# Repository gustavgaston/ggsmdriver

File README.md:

# GGSMDriver

A small, reusable stepper driver module: STM32G0B1 + TMC2209, one 9–24 V supply
and a 4-wire motor on one row of screw terminals along one edge, and USB-C for serial
and firmware upload. The board is 4 layers, 55×45 mm, with every
part on top, for JLCPCB assembly.

## Layout

| Path | What |
|---|---|
| `requirements.md` | Circuit spec, pin map, parts with LCSC numbers, confirmed decisions |
| `PLAN.md` | Milestones |
| `HANDOFF.md` | Current state and how to regenerate everything (start here when resuming) |
| `hardware/ggsmdriver.py` | The design as Python: parts, pin→net map, PCB placement |
| `hardware/ggsmdriver.kicad_sym` | Custom TMC2209 symbol |
| `kicad/` | Generated KiCad project (schematic, PCB, PDF) and `reports/` |
| `kicad/fab/` | JLCPCB gerbers zip, BOM and placement (CPL) files |
| `firmware/` | STM32 HAL firmware: ggstepper core + Automato over USB serial (see its README) |

The KiCad files are generated by [autopcb](https://github.com/gustavgaston/autopcb)
from `hardware/ggsmdriver.py`; hand edits in KiCad are lost on regeneration.
They are KiCad 7 format and open in KiCad 10.

## Status

- Schematic: done (ERC clean in KiCad 10).
- PCB: generated and fully routed as a practice run; routing, placement and
  silkscreen to be reworked later.
- Fab files: generated.
- Firmware: ported and building; untested on hardware.

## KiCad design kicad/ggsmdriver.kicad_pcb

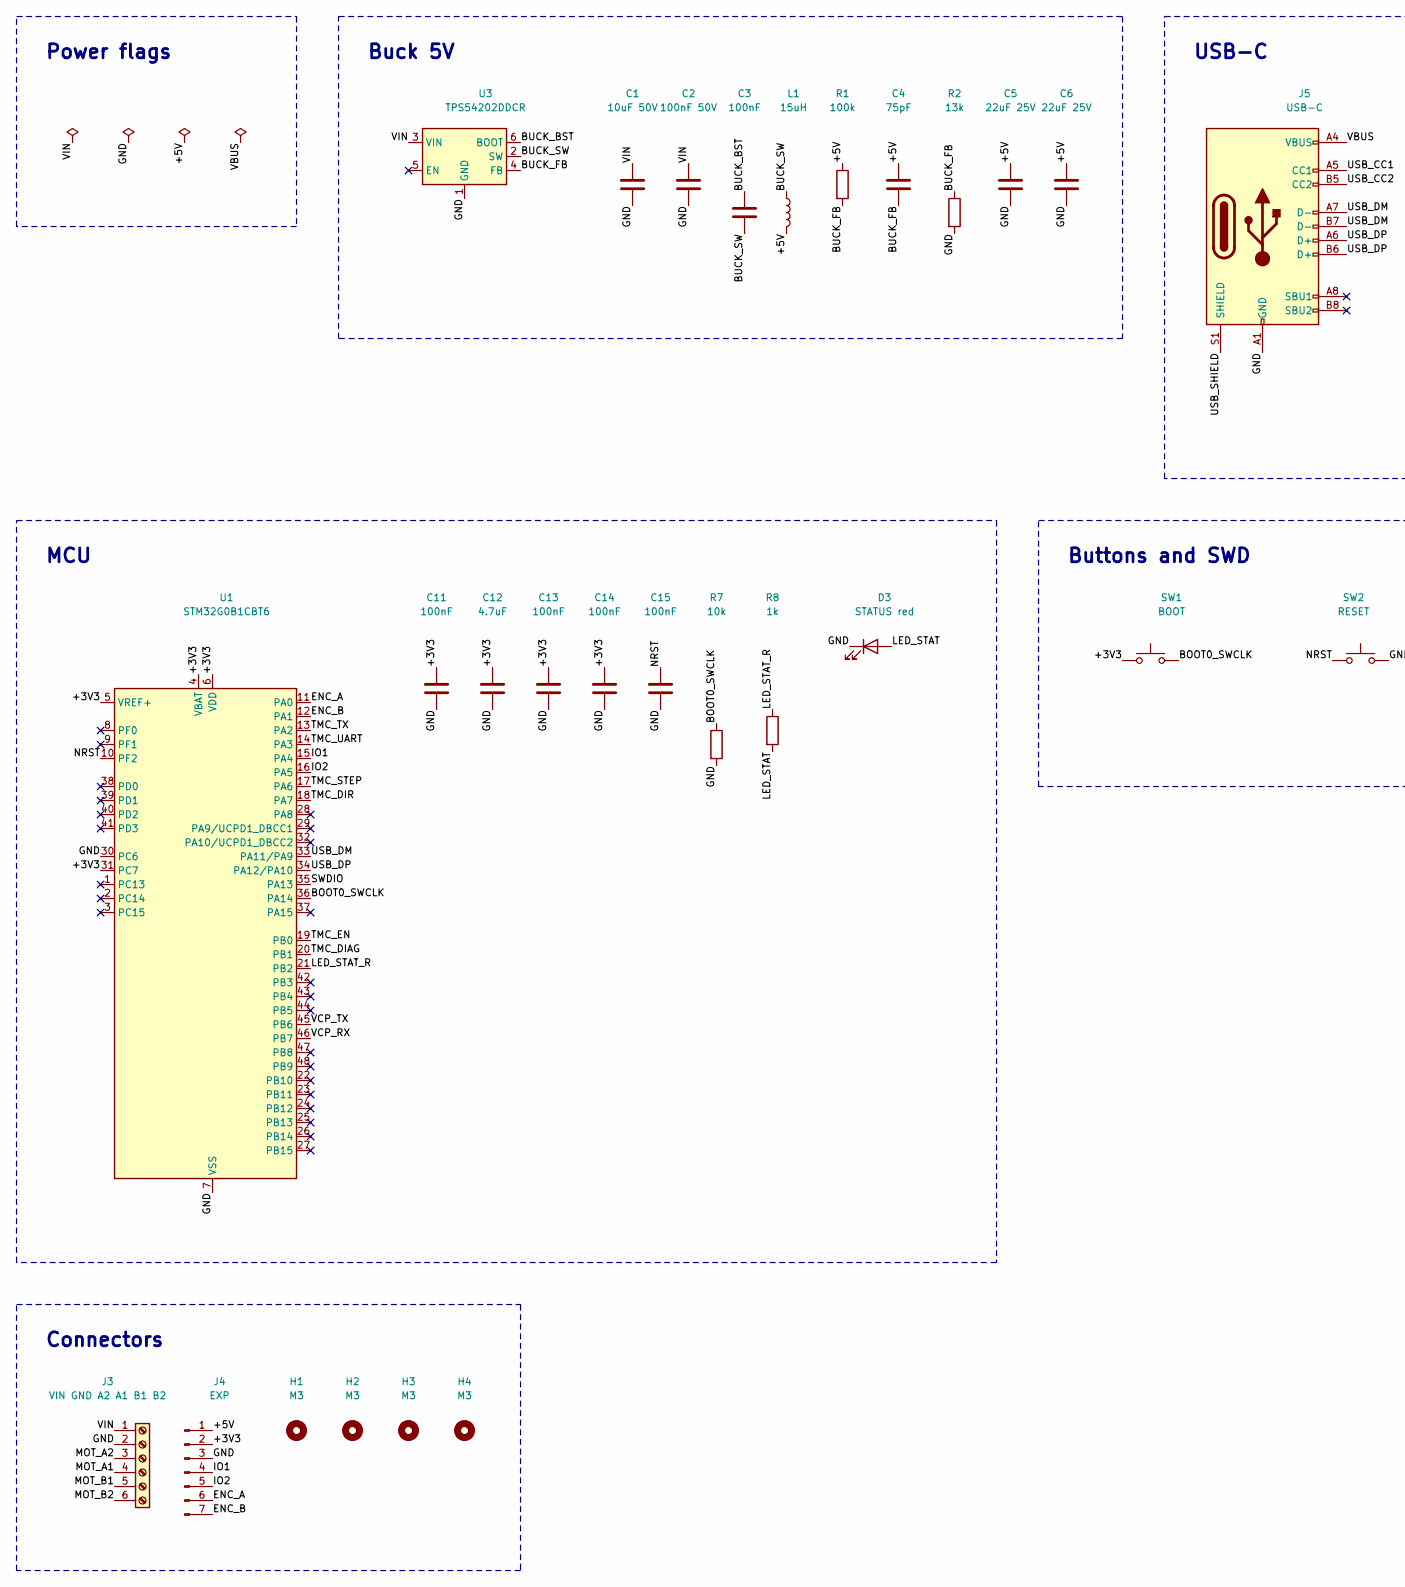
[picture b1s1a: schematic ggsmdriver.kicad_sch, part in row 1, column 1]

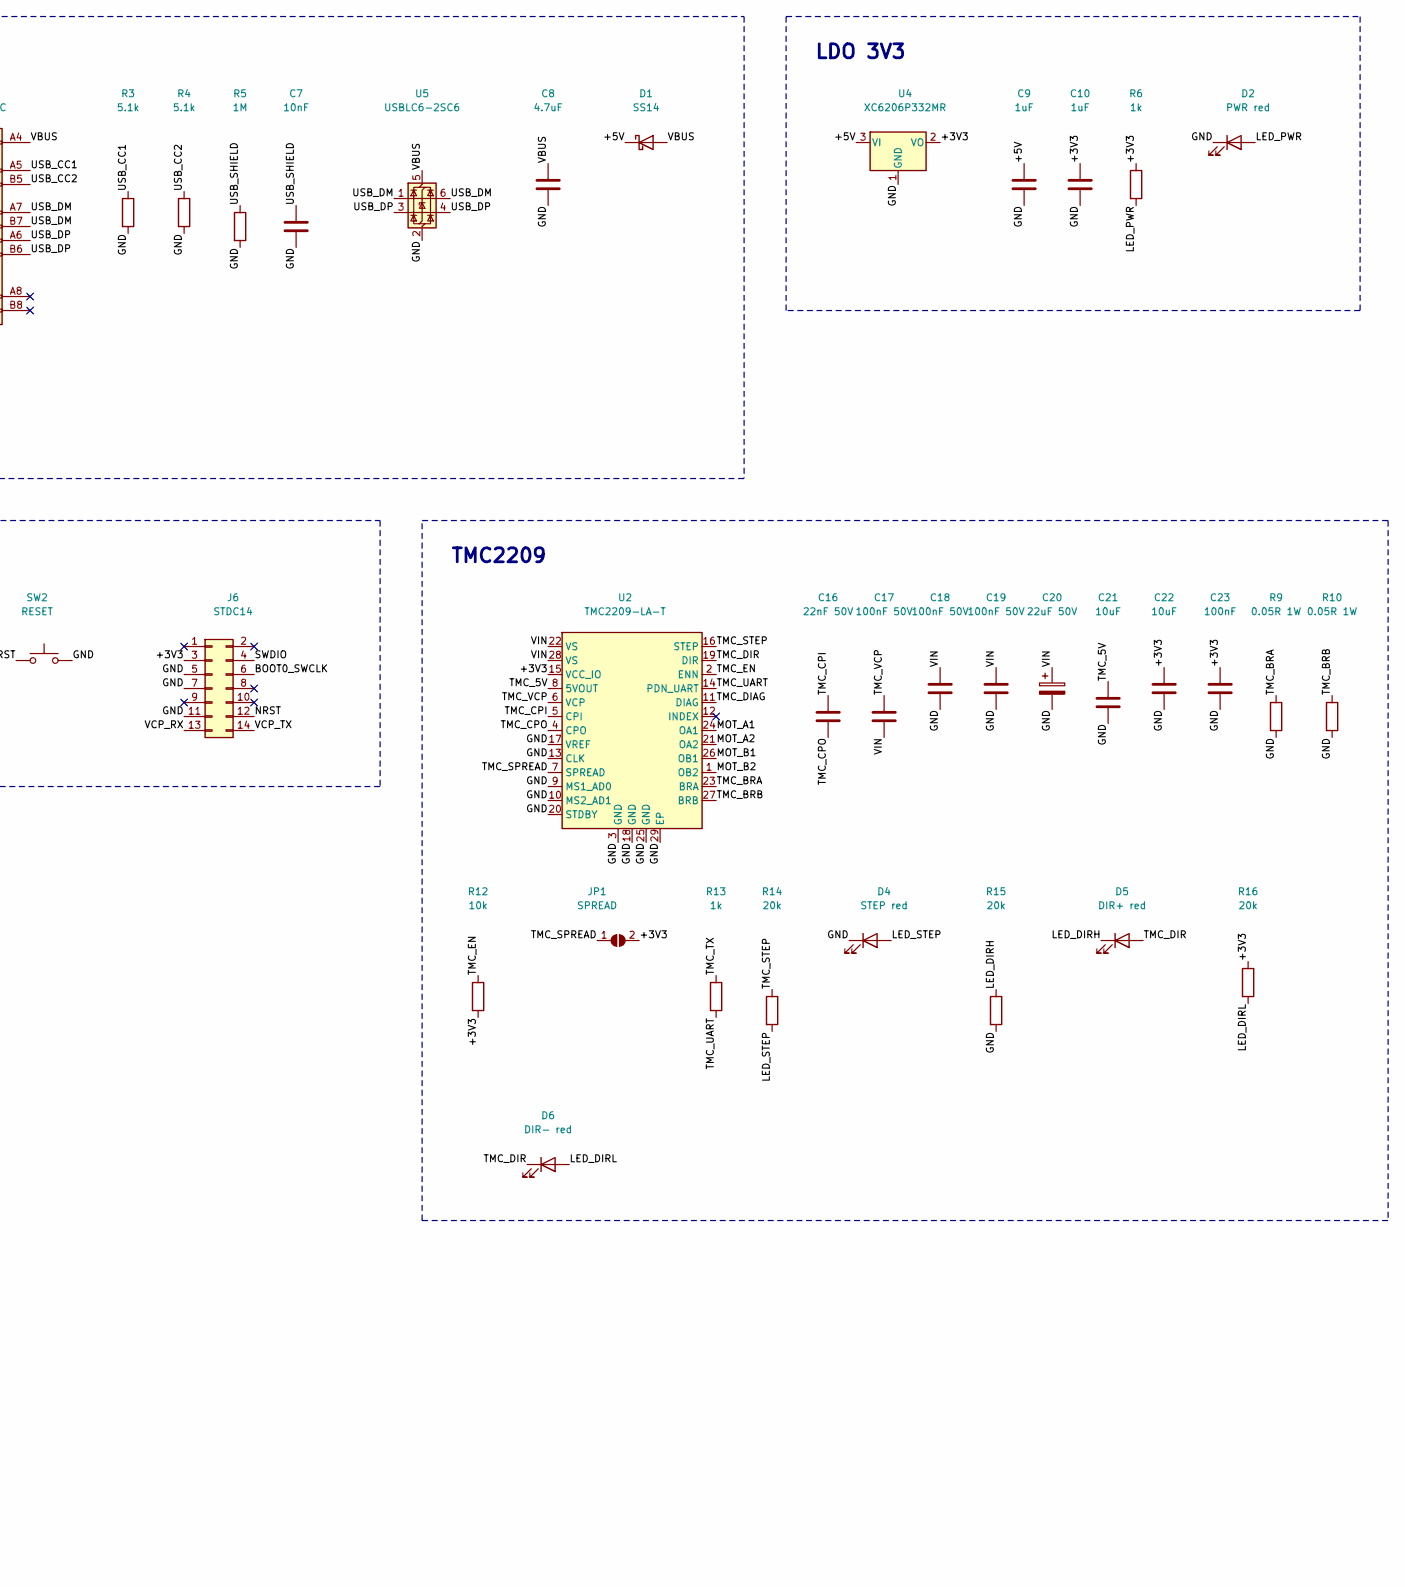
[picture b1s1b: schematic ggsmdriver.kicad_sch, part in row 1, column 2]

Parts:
C1: 10uF 50V; C_1206_3216Metric; LCSC C13585
C2, C17, C18, C19: 100nF 50V; C_0603_1608Metric; LCSC C14663
C3, C11, C13, C14, C15, C23: 100nF; C_0603_1608Metric; LCSC C14663
C4: 75pF; C_0603_1608Metric; LCSC C1681
C5, C6: 22uF 25V; C_1206_3216Metric; LCSC C12891
C7: 10nF; C_0603_1608Metric; LCSC C57112
C8, C12: 4.7uF; C_0805_2012Metric; LCSC C1779
C9, C10: 1uF; C_0603_1608Metric; LCSC C15849
C16: 22nF 50V; C_0603_1608Metric; LCSC C21122
C20: 22uF 50V; CP_Elec_6.3x5.4; LCSC C176676
C21, C22: 10uF; C_0805_2012Metric; LCSC C15850
D1: SS14; D_SMA; LCSC C2480
D2: PWR red; LED_0603_1608Metric; LCSC C2286
D3: STATUS red; LED_0603_1608Metric; LCSC C2286
D4: STEP red; LED_0603_1608Metric; LCSC C2286
D5: DIR+ red; LED_0603_1608Metric; LCSC C2286
D6: DIR- red; LED_0603_1608Metric; LCSC C2286
H1, H2, H3, H4: M3; MountingHole_3.2mm_M3
J3: VIN GND A2 A1 B1 B2; TerminalBlock_Phoenix_MPT-0,5-6-2.54_1x06_P2.54mm_Horizontal; LCSC C474924
J4: EXP; PinHeader_1x07_P2.54mm_Vertical
J5: USB-C; USB_C_Receptacle_HRO_TYPE-C-31-M-12; LCSC C165948
J6: STDC14; PinHeader_2x07_P1.27mm_Vertical_SMD
JP1: SPREAD; SolderJumper-2_P1.3mm_Open_RoundedPad1.0x1.5mm
L1: 15uH; L_Bourns_SRN6045TA; LCSC C467142
R1: 100k; R_0603_1608Metric; LCSC C25803
R2: 13k; R_0603_1608Metric; LCSC C22797
R3, R4: 5.1k; R_0603_1608Metric; LCSC C23186
R5: 1M; R_0603_1608Metric; LCSC C22935
R6, R8, R13: 1k; R_0603_1608Metric; LCSC C21190
R7, R12: 10k; R_0603_1608Metric; LCSC C25804
R9, R10: 0.05R 1W; R_1206_3216Metric; LCSC C154645
R14, R15, R16: 20k; R_0603_1608Metric; LCSC C4184
SW1: BOOT; SW_Push_1P1T_XKB_TS-1187A; LCSC C318884
SW2: RESET; SW_Push_1P1T_XKB_TS-1187A; LCSC C318884
U1: STM32G0B1CBT6; LQFP-48_7x7mm_P0.5mm; LCSC C2847904
U2: TMC2209-LA-T; QFN-28-1EP_5x5mm_P0.5mm_EP3.35x3.35mm; LCSC C2150710
U3: TPS54202DDCR; TSOT-23-6; LCSC C191884
U4: XC6206P332MR; SOT-23; LCSC C5446
U5: USBLC6-2SC6; SOT-23-6; LCSC C7519

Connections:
+3V3: C10.1, C11.1, C12.1, C13.1, C14.1, C22.1, C23.1, J4.2, J6.3, JP1.2 (B), R6.1, R12.2, R16.1, SW1.1, U1.4 (VBAT), U1.5 (VREF+), U1.6 (VDD), U1.31 (PC7), U2.15 (VCC_IO), U4.2 (VO)
+5V: C4.1, C5.1, C6.1, C9.1, D1.1 (K), J4.1, L1.2, R1.1, U4.3 (VI)
BOOT0_SWCLK: J6.6, R7.1, SW1.2, U1.36 (PA14)
BUCK_BST: C3.1, U3.6 (BOOT)
BUCK_FB: C4.2, R1.2, R2.1, U3.4 (FB)
BUCK_SW: C3.2, L1.1, U3.2 (SW)
ENC_A: J4.6, U1.11 (PA0)
ENC_B: J4.7, U1.12 (PA1)
GND: C1.2, C2.2, C5.2, C6.2, C7.2, C8.2, C9.2, C10.2, C11.2, C12.2, C13.2, C14.2, C15.2, C18.2, C19.2, C20.2, C21.2, C22.2, C23.2, D2.1 (K), D3.1 (K), D4.1 (K), J3.2, J4.3, J5.A1 (GND), J5.A12 (GND), J5.B1 (GND), J5.B12 (GND), J6.5, J6.7, J6.11, R2.2, R3.2, R4.2, R5.2, R7.2, R9.2, R10.2, R15.2, SW2.2, U1.7 (VSS), U1.30 (PC6), U2.3 (GND), U2.9 (MS1_AD0), U2.10 (MS2_AD1), U2.13 (CLK), U2.17 (VREF), U2.18 (GND), U2.20 (STDBY), U2.25 (GND), U2.29 (EP), U3.1 (GND), U4.1 (GND), U5.2 (GND)
IO1: J4.4, U1.15 (PA4)
IO2: J4.5, U1.16 (PA5)
LED_DIRH: D5.1 (K), R15.1
LED_DIRL: D6.2 (A), R16.2
LED_PWR: D2.2 (A), R6.2
LED_STAT: D3.2 (A), R8.2
LED_STAT_R: R8.1, U1.21 (PB2)
LED_STEP: D4.2 (A), R14.2
MOT_A1: J3.4, U2.24 (OA1)
MOT_A2: J3.3, U2.21 (OA2)
MOT_B1: J3.5, U2.26 (OB1)
MOT_B2: J3.6, U2.1 (OB2)
NRST: C15.1, J6.12, SW2.1, U1.10 (PF2)
SWDIO: J6.4, U1.35 (PA13)
TMC_5V: C21.1, U2.8 (5VOUT)
TMC_BRA: R9.1, U2.23 (BRA)
TMC_BRB: R10.1, U2.27 (BRB)
TMC_CPI: C16.1, U2.5 (CPI)
TMC_CPO: C16.2, U2.4 (CPO)
TMC_DIAG: U1.20 (PB1), U2.11 (DIAG)
TMC_DIR: D5.2 (A), D6.1 (K), U1.18 (PA7), U2.19 (DIR)
TMC_EN: R12.1, U1.19 (PB0), U2.2 (ENN)
TMC_SPREAD: JP1.1 (A), U2.7 (SPREAD)
TMC_STEP: R14.1, U1.17 (PA6), U2.16 (STEP)
TMC_TX: R13.1, U1.13 (PA2)
TMC_UART: R13.2, U1.14 (PA3), U2.14 (PDN_UART)
TMC_VCP: C17.1, U2.6 (VCP)
USB_CC1: J5.A5 (CC1), R3.1
USB_CC2: J5.B5 (CC2), R4.1
USB_DM: J5.A7 (D-), J5.B7 (D-), U1.33 (PA11/PA9), U5.1 (I/O1), U5.6 (I/O1)
USB_DP: J5.A6 (D+), J5.B6 (D+), U1.34 (PA12/PA10), U5.3 (I/O2), U5.4 (I/O2)
USB_SHIELD: C7.1, J5.S1 (SHIELD), R5.1
VBUS: C8.1, D1.2 (A), J5.A4 (VBUS), J5.A9 (VBUS), J5.B4 (VBUS), J5.B9 (VBUS), U5.5 (VBUS)
VCP_RX: J6.13, U1.46 (PB7)
VCP_TX: J6.14, U1.45 (PB6)
VIN: C1.1, C2.1, C17.2, C18.1, C19.1, C20.1, J3.1, U2.22 (VS), U2.28 (VS), U3.3 (VIN)

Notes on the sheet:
Power flags
Buck 5V
USB-C
LDO 3V3
MCU
Buttons and SWD
TMC2209
Connectors

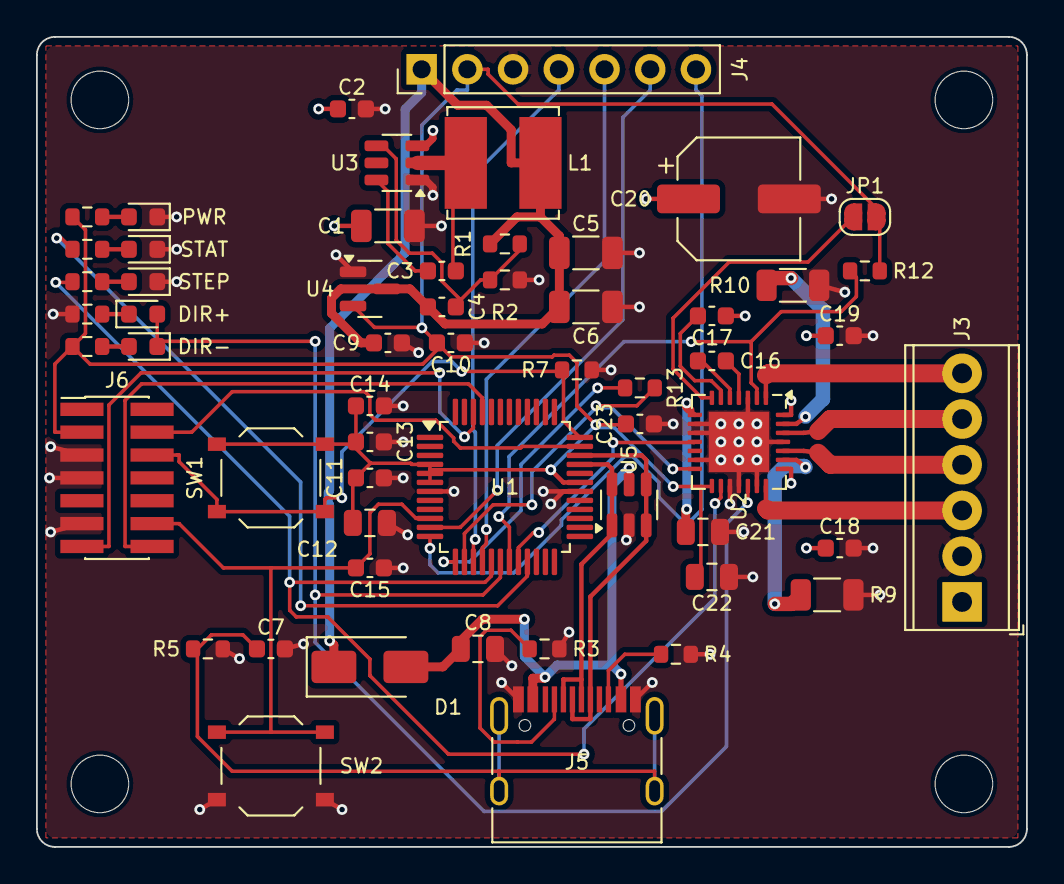
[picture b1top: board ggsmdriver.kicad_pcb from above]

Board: 4 copper layers, 55.0 x 45.0 mm, 61 parts (0 on the bottom side), 45 nets.

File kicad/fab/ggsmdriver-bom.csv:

Comment,Designator,Footprint,LCSC Part #
10uF 50V,C1,C_1206_3216Metric,C13585
22nF 50V,C16,C_0603_1608Metric,C21122
100nF 50V,"C2,C17,C18,C19",C_0603_1608Metric,C14663
22uF 50V,C20,CP_Elec_6.3x5.4,C176676
10uF,"C21,C22",C_0805_2012Metric,C15850
100nF,"C3,C11,C13,C14,C15,C23",C_0603_1608Metric,C14663
75pF,C4,C_0603_1608Metric,C1681
22uF 25V,"C5,C6",C_1206_3216Metric,C12891
10nF,C7,C_0603_1608Metric,C57112
4.7uF,"C8,C12",C_0805_2012Metric,C1779
1uF,"C9,C10",C_0603_1608Metric,C15849
SS14,D1,D_SMA,C2480
PWR red,D2,LED_0603_1608Metric,C2286
STATUS red,D3,LED_0603_1608Metric,C2286
STEP red,D4,LED_0603_1608Metric,C2286
DIR+ red,D5,LED_0603_1608Metric,C2286
DIR- red,D6,LED_0603_1608Metric,C2286
VIN GND A2 A1 B1 B2,J3,"TerminalBlock_Phoenix_MPT-0,5-6-2.54_1x06_P2.54mm_Horizontal",C474924
USB-C,J5,USB_C_Receptacle_HRO_TYPE-C-31-M-12,C165948
15uH,L1,L_Bourns_SRN6045TA,C467142
100k,R1,R_0603_1608Metric,C25803
20k,"R14,R15,R16",R_0603_1608Metric,C4184
13k,R2,R_0603_1608Metric,C22797
5.1k,"R3,R4",R_0603_1608Metric,C23186
1M,R5,R_0603_1608Metric,C22935
1k,"R6,R8,R13",R_0603_1608Metric,C21190
10k,"R7,R12",R_0603_1608Metric,C25804
0.05R 1W,"R9,R10",R_1206_3216Metric,C154645
BOOT,SW1,SW_Push_1P1T_XKB_TS-1187A,C318884
RESET,SW2,SW_Push_1P1T_XKB_TS-1187A,C318884
STM32G0B1CBT6,U1,LQFP-48_7x7mm_P0.5mm,C2847904
TMC2209-LA-T,U2,QFN-28-1EP_5x5mm_P0.5mm_EP3.35x3.35mm,C2150710
TPS54202DDCR,U3,TSOT-23-6,C191884
XC6206P332MR,U4,SOT-23,C5446
USBLC6-2SC6,U5,SOT-23-6,C7519

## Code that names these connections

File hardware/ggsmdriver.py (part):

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    s.add("U1", "MCU_ST_STM32G0:STM32G0B1CBTx", "STM32G0B1CBT6",
          "Package_QFP:LQFP-48_7x7mm_P0.5mm",
          {"VDD": "+3V3", "VSS": "GND", "VBAT": "+3V3", "VREF+": "+3V3",
           "PF2": "NRST", "PA14": "BOOT0_SWCLK", "PA13": "SWDIO",
           "33": "USB_DM", "34": "USB_DP",
           "PA0": "ENC_A", "PA1": "ENC_B", "PA2": "TMC_TX", "PA3": "TMC_UART",
           "PA4": "IO1", "PA5": "IO2", "PA6": "TMC_STEP", "PA7": "TMC_DIR",
           "PB0": "TMC_EN", "PB1": "TMC_DIAG", "PB2": "LED_STAT_R",
           "PB6": "VCP_TX", "PB7": "VCP_RX",  # USART1 to the STLINK virtual COM port
           # PC6/PC7 here are VSS/VDDIO2 on the CBT6N, so either part fits.
           "PC6": "GND", "PC7": "+3V3"}, b, {"LCSC": "C2847904"})
    c("C11", "100nF", "+3V3", "GND", b)
    c("C12", "4.7uF", "+3V3", "GND", b, C0805)
    c("C13", "100nF", "+3V3", "GND", b)  # VREF+
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    # STDC14 debug connector for the STLINK-V3MINIE flat cable (replaces the SWD test pads).
    # Samtec FTSH-107-01-L-DV-K (keyed shroud, mates FFSD), hand-soldered: no LCSC number.
    # 1, 2, 9 reserved; 8 SWO and 10 JTDI unused (Cortex-M0+ has no SWO); 11 GNDDetect.
    # 13/14 are the probe's virtual COM port, wired to USART1 (PB7 RX, PB6 TX).
    s.add("J6", "Connector_Generic:Conn_02x07_Odd_Even", "STDC14",
          "Connector_PinHeader_1.27mm:PinHeader_2x07_P1.27mm_Vertical_SMD",
          {"3": "+3V3", "4": "SWDIO", "5": "GND", "6": "BOOT0_SWCLK", "7": "GND",
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    s.add("JP1", "Jumper:SolderJumper_2_Open", "SPREAD",
          "Jumper:SolderJumper-2_P1.3mm_Open_RoundedPad1.0x1.5mm",
          {"A": "TMC_SPREAD", "B": "+3V3"}, b)
    r("R13", "1k", "TMC_TX", "TMC_UART", b)  # datasheet 2-pin UART; RX is direct
    # Activity LEDs as on Adafruit: STEP, DIR high, DIR low (all red here).
    r("R14", "20k", "TMC_STEP", "LED_STEP", b)
    led("D4", "STEP red", "LED_STEP", "GND", b)
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            b.via(ux + dx, uy + dy, "GND")
    b.tie("U2", ["3", "9", "10", "13", "18", "20", "25"], "29")  # GND pins to the pad

    b.netclass("Power", ["VIN", "+5V", "VBUS", "TMC_5V"], track=0.5)  # +3V3 stays 0.2: MCU pins
    b.netclass("USB", ["USB_DP", "USB_DM"], track=0.25, clearance=0.15)
    b.netclass("Motor", ["MOT_A1", "MOT_A2", "MOT_B1", "MOT_B2",
                         "TMC_BRA", "TMC_BRB"], track=0.8)
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
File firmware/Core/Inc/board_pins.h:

/* GGSMDriver pin map. Source: /requirements.md (pin map table), verified
   against the schematic generator (hardware/ggsmdriver.py) for the LED.
   Pins not listed here (PA0/PA1 encoder, PA4/PA5 IO1/IO2, PA11/PA12 USB,
   PA13/PA14 SWD) are not configured by this firmware. */
#ifndef BOARD_PINS_H
#define BOARD_PINS_H

#include "stm32g0xx_hal.h"

/* TMC2209 STEP. The pin is TIM3_CH1, but the firmware drives it as a plain
   output: TIM3 only times the compare interrupt (see ggstepper_hw.c). */
#define TMC_STEP_PORT GPIOA
#define TMC_STEP_PIN GPIO_PIN_6
#define TMC_DIR_PORT GPIOA
#define TMC_DIR_PIN GPIO_PIN_7
/* ENN, active low, external pull-up: the driver is off until the MCU enables it. */
#define TMC_EN_PORT GPIOB
#define TMC_EN_PIN GPIO_PIN_0
/* DIAG on EXTI line 1. */
#define TMC_DIAG_PORT GPIOB
#define TMC_DIAG_PIN GPIO_PIN_1
#define TMC_DIAG_IRQn EXTI0_1_IRQn
/* Status LED: PB2 -> 1 k -> LED -> GND, so high = on. */
#define LED_STATUS_PORT GPIOB
#define LED_STATUS_PIN GPIO_PIN_2

/* TMC2209 UART on USART2: PA2 TX (through 1 k to PDN_UART), PA3 RX (direct
   to PDN_UART, so every transmitted byte is echoed on RX). */
#define TMC_UART_INSTANCE USART2
#define TMC_UART_PORT GPIOA
#define TMC_UART_TX_PIN GPIO_PIN_2
#define TMC_UART_RX_PIN GPIO_PIN_3
#define TMC_UART_AF GPIO_AF1_USART2

#endif
